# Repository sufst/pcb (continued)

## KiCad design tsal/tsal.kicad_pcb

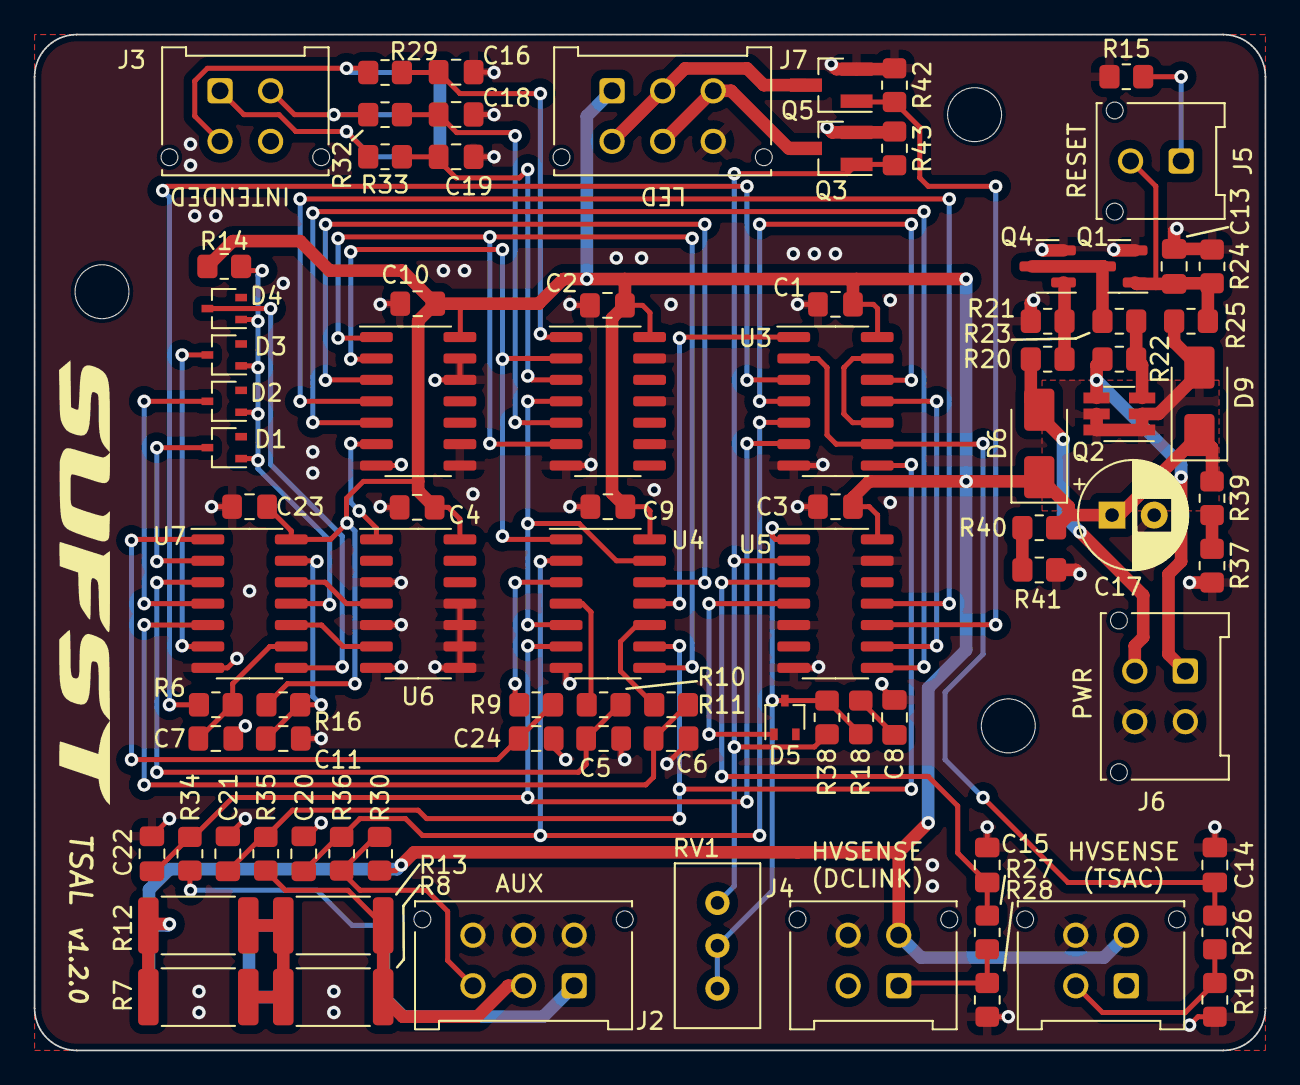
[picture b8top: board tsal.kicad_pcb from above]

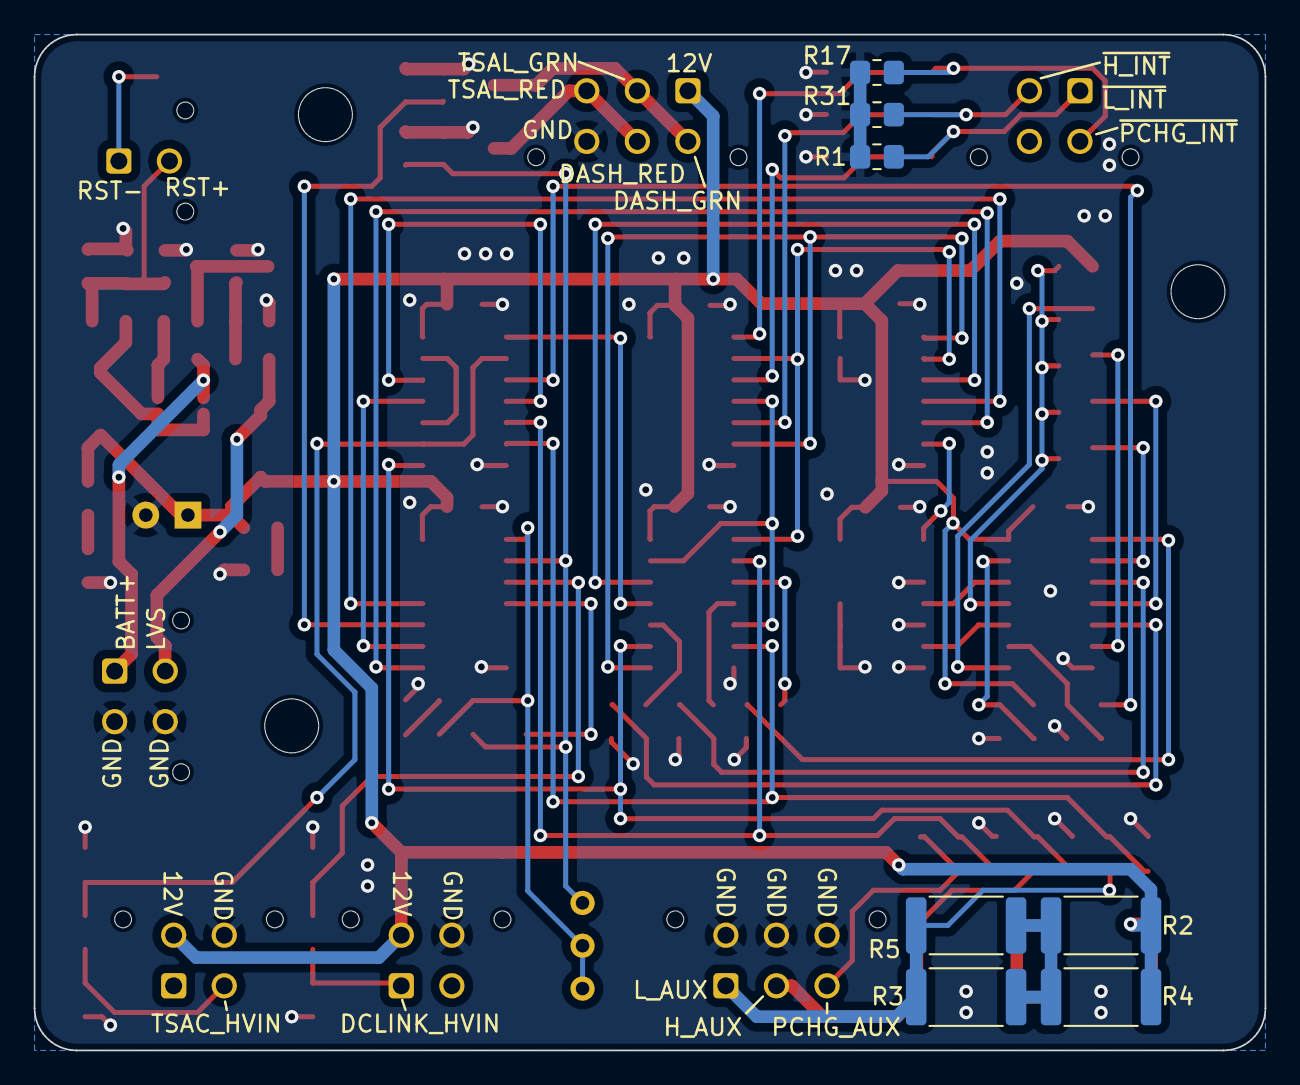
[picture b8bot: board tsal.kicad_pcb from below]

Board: 2 copper layers, 73.0 x 60.2 mm, 96 parts (7 on the bottom side), 64 nets.

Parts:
C1, C2, C3, C4, C9, C10, C13, C14, C15, C16, C18, C19, C20, C21, C22, C23: 100n; C_0805_2012Metric_Pad1.18x1.45mm_HandSolder
C5, C6, C7, C8, C11, C24: 10u; C_0805_2012Metric_Pad1.18x1.45mm_HandSolder
C17: 100u; CP_Radial_D6.3mm_P2.50mm
D1, D2, D3, D4, D5: BAT54W; SOT-323_SC-70
D6, D9: SS14+; D_SMA
H1, H2, H3: MountingHole; MountingHole_3.2mm_M3
J1, J3, J4, J6: Conn_01x04; Molex_Micro-Fit_3.0_43045-0412_2x02_P3.00mm_Vertical
J2, J7: Conn_01x06; Molex_Micro-Fit_3.0_43045-0612_2x03_P3.00mm_Vertical
J5: Conn_01x02; Molex_Micro-Fit_3.0_43045-0212_2x01_P3.00mm_Vertical
Q1, Q4: XP262N7002TR-G; SOT-23
Q2: DMP3056LDM; SOT-23-6_Handsoldering
Q3, Q5: FDN359BN; SOT-23_Handsoldering
R1, R9, R10, R11, R14, R16, R17, R18, R19, R21, R23, R25, R26, R27, R28, R29, R30, R31, R32, R33, R34, R35, R36, R42, R43: 10k; R_0805_2012Metric_Pad1.20x1.40mm_HandSolder
R2, R3, R4, R5, R7, R8, R12, R13: 270; R_2512_6332Metric
R6, R22, R24, R38: 100k; R_0805_2012Metric_Pad1.20x1.40mm_HandSolder
R15: 47; R_0805_2012Metric_Pad1.20x1.40mm_HandSolder
R20, R37, R39, R40, R41: 1k; R_0805_2012Metric_Pad1.20x1.40mm_HandSolder
RV1: 470k; Potentiometer_Bourns_3296W_Vertical
U1: 4071; SOIC-14_3.9x8.7mm_P1.27mm
U2, U4: 4081; SOIC-14_3.9x8.7mm_P1.27mm
U3, U5, U7: 40106; SOIC-14_3.9x8.7mm_P1.27mm
U6: 4013; SOIC-14_3.9x8.7mm_P1.27mm

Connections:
+12V: C1.1, C2.1, C3.1, C4.1, C9.1, C10.1, C17.1, C23.1, D6.1 (K), D9.1 (K), J1.3, J4.3, J7.1, R2.1, R4.1, R7.1, R12.1, R14.2, R16.2, R30.1, R39.1, R40.1, U1.14 (VDD), U2.14 (VDD), U3.14 (VDD), U4.14 (VDD), U5.14 (VDD), U6.14 (VDD), U7.14 (VDD)
/BATT+: J6.1, Q2.4 (S), R22.2
/DCLINK_HV_DETECTED: C15.1, R27.1, U5.3
/GREEN_LED_ON: Q5.1 (G), R42.2, U5.10
/Implausibility and LED logic/HIGH_AIR_INTENDED_ON: U1.1, U3.6, U4.8
/Implausibility and LED logic/IMPLAUSIBLE: U1.6, U6.1 (Q)
/Implausibility and LED logic/LOW_AIR_INTENDED_ON: U3.4, U4.5, U4.13
/Implausibility and LED logic/POR: U6.4 (R), U7.12
/Implausibility and LED logic/PRCHG_INTENDED_ON: U1.2, U3.2, U4.1
/LVS: D6.2 (A), J6.3, R20.2
/Power Latch/LATCH_RESET+: C13.1, J5.2, Q1.1 (G), R24.2, R25.1
/Power Latch/LATCH_RESET-: J5.1, R15.2
/RED_LED_ON: Q3.1 (G), R38.2, R43.2, RV1.1, U5.2
/~HIGH_AIR_INTENDED_ON: C18.1, R32.1, U3.5
/~HIGH_AIR_MECH_ON: C21.1, R35.1, U2.8, U4.9
/~LOW_AIR_INTENDED_ON: C19.1, R33.1, U3.3
/~LOW_AIR_MECH_ON: C22.1, R34.1, U2.6, U4.6
/~PRCHG_INTENDED_ON: C16.1, R29.1, U3.1
/~PRCHG_MECH_ON: C20.1, R36.1, U2.5, U4.2
/~TSAC_HV_DETECTED: C14.1, R26.1, U2.2, U2.9
GND: C1.2, C2.2, C3.2, C4.2, C5.2, C6.2, C7.2, C8.2, C9.2, C10.2, C11.2, C13.2, C14.2, C15.2, C16.2, C17.2, C18.2, C19.2, C20.2, C21.2, C22.2, C23.2, C24.2, J1.4, J2.4, J2.5, J2.6, J4.4, J6.2, J6.4, J7.6, Q1.2 (S), Q3.2 (S), Q4.2 (S), Q5.2 (S), R1.2, R15.1, R17.2, R19.1, R21.1, R24.1, R28.1, R31.2, R37.2, R41.2, R42.1, R43.1, U1.7 (VSS), U1.8, U1.9, U1.12, U1.13, U2.7 (VSS), U3.7 (VSS), U3.9, U3.11, U3.13, U4.7 (VSS), U5.5, U5.7 (VSS), U5.13, U6.3 (C), U6.5 (D), U6.7 (VSS), U6.8 (S), U6.9 (D), U6.10 (R), U6.11 (C), U7.7 (VSS)
unnamed: C5.1, R10.2, U7.3
unnamed: C6.1, R11.2, U7.5
unnamed: C7.1, R6.2, U7.9
unnamed: C8.1, R18.1
unnamed: C11.1, R16.1, U7.13
unnamed: C24.1, R9.2, U7.1
unnamed: D1.1 (A), D2.1 (A), D3.1 (A), D4.1 (A), R14.1, U7.11
unnamed: D1.3 (K), U7.2
unnamed: D2.3 (K), U7.4
unnamed: D3.3 (K), U7.6
unnamed: D4.3 (K), U7.8
unnamed: D5.1 (A), U5.4
unnamed: D5.3 (K), R18.2, R38.1, RV1.2, RV1.3, U5.1
unnamed: D9.2 (A), Q2.1 (D), Q2.2 (D), Q2.5 (D), Q2.6 (D), R25.2
unnamed: J1.2, R19.2, R26.2
unnamed: J2.1, R3.2, R5.2, R34.2
unnamed: J2.2, R8.2, R13.2, R35.2
unnamed: J2.3, R30.2, R36.2
unnamed: J3.1, R1.1, R33.2
unnamed: J3.2, R31.1, R32.2
unnamed: J3.3, R17.1, R29.2
unnamed: J4.1, R27.2, R28.2
unnamed: J7.2, J7.4, Q5.3 (D)
unnamed: J7.3, J7.5, Q3.3 (D)
unnamed: Q1.3 (D), Q4.3 (D), R23.1
unnamed: Q2.3 (G), R22.1, R23.2
unnamed: Q4.1 (G), R20.1, R21.2
unnamed: R2.2, R3.1, R4.2, R5.1
unnamed: R6.1, U2.3
unnamed: R9.1, U4.3
unnamed: R10.1, U4.4
unnamed: R11.1, U4.10
unnamed: R7.2, R8.1, R12.2, R13.1
unnamed: R37.1, R39.2
unnamed: R40.2, R41.1
unnamed: U1.3, U4.12
unnamed: U1.4, U5.11
unnamed: U1.5, U5.8
unnamed: U2.1, U4.11
unnamed: U2.10, U2.13
unnamed: U2.11, U5.9
unnamed: U2.4, U2.12
unnamed: U6.6 (S), U7.10
